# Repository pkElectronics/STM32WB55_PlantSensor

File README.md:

# STM32WB55_PlantSensor
Project goal (for the first stage) is to develop an IOT System based on the STM32WB SoC to monitor soil and air Moisture as well as environment temperature.
Therefore several components will be developed including a battery powered sensor to stick into your flower pots and a base station to display and log the measurements from the sensors. 
Communication between the sensors and the base will be done via bluetooth mesh. Later more kinds of sensors may be developed as well.

All Hardware Design Files licensed under CC BY-NC 4.0 

https://creativecommons.org/licenses/by-nc/4.0/legalcode

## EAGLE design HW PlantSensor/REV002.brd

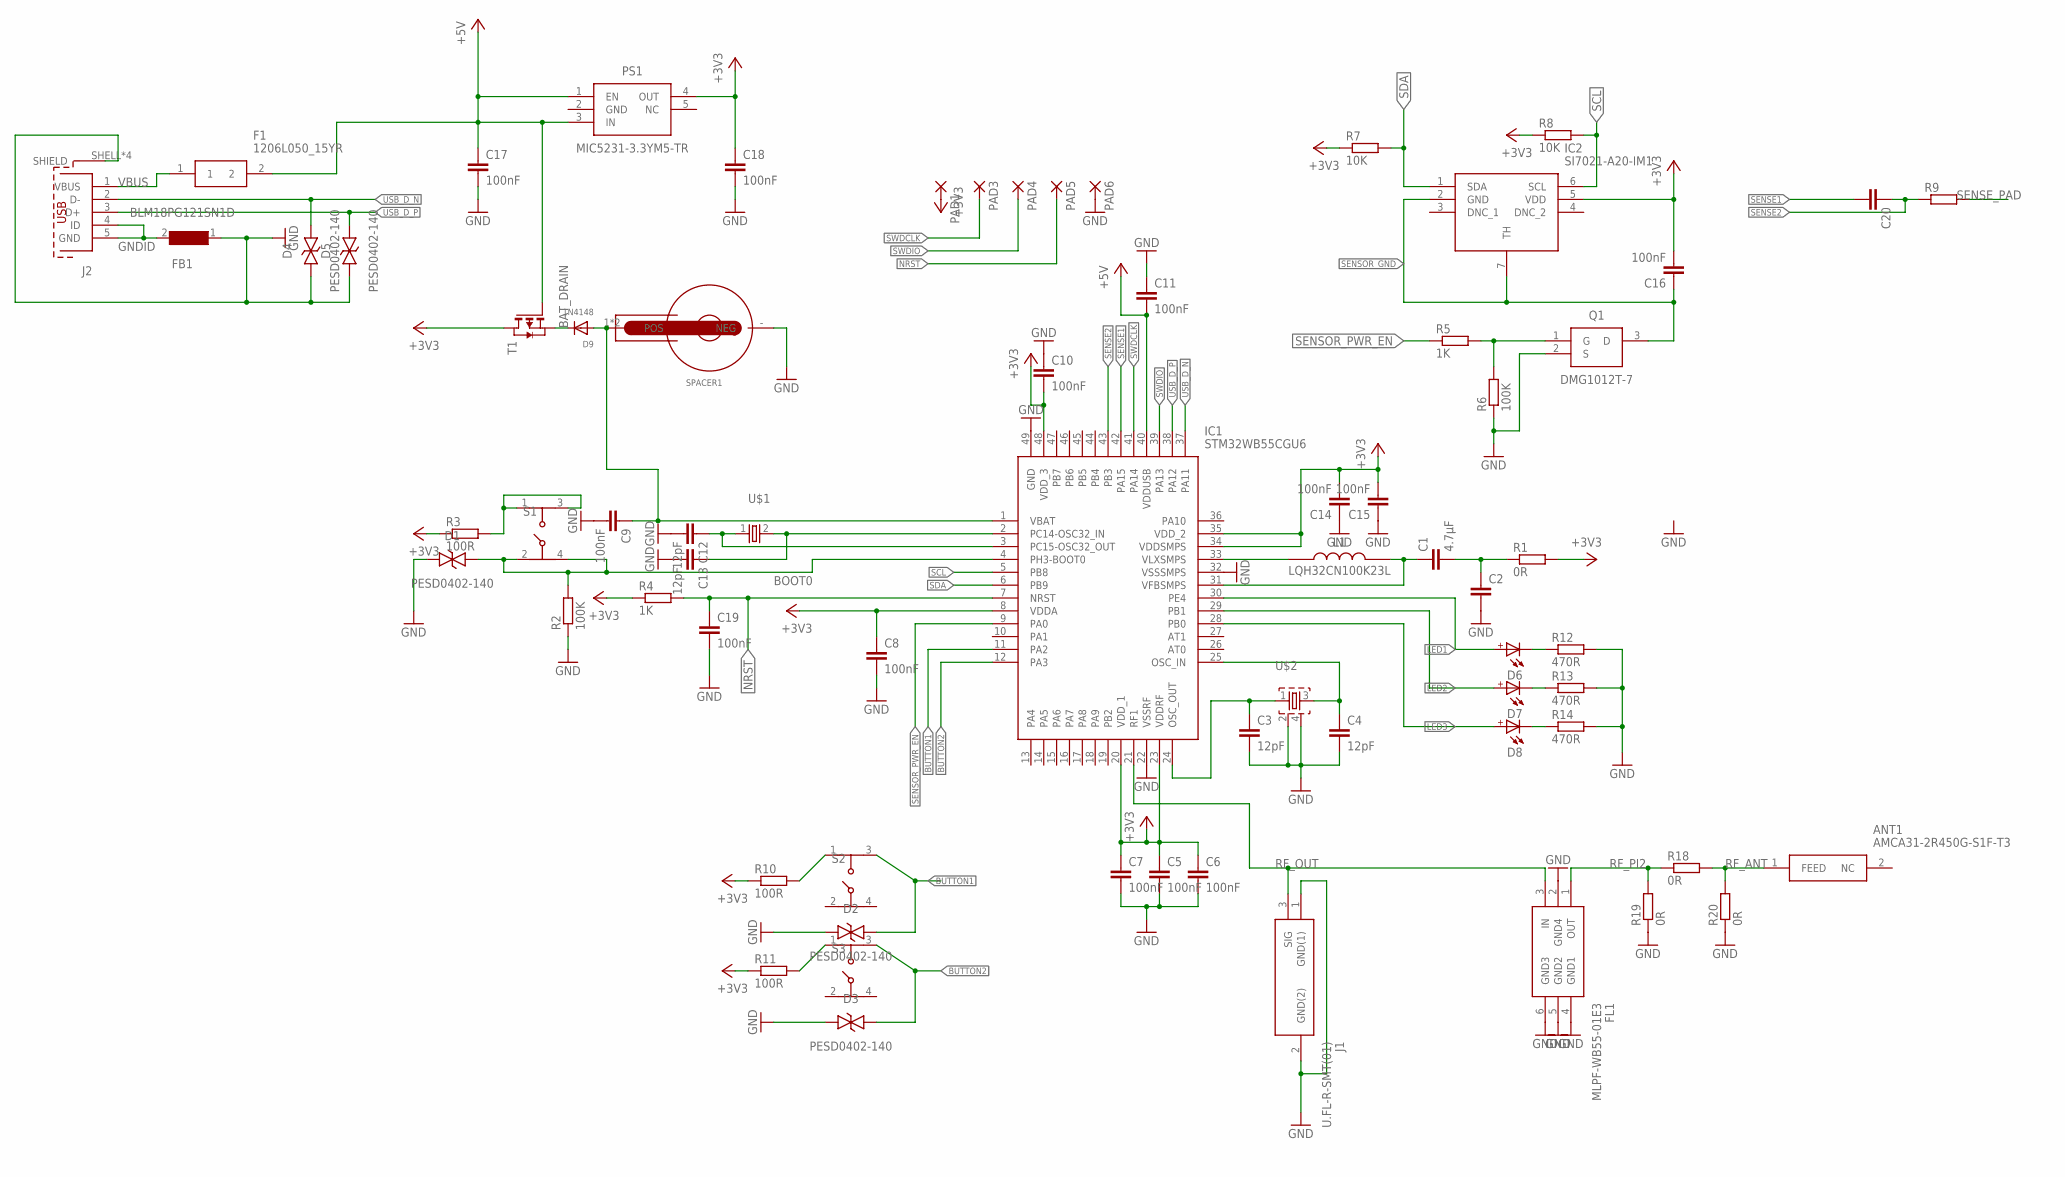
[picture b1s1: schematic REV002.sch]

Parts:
ANT1: AMCA31-2R450G-S1F-T3; ANTC3216X140N
C1: 4.7µF; C1210K
C2, C20: C-EUC0402K; C0402K
C3, C4, C12, C13: 12pF; C0402K
C5, C6, C7, C8, C9, C10, C11, C14, C15, C16, C17, C18, C19: 100nF; C0402K
D1, D2, D3, D4, D5: PESD0402-140; DIONC1005X43N
D6, D7, D8: WL-SMCD_0603_150060BS55040; WL-SMCD_0603
D9: 1N4148; SOD-323F
F1: 1206L050_15YR; FUSC3216X75N
FB1: BLM18PG121SN1D; BEADC1608X95N
FL1: MLPF-WB55-01E3; MLPFWB5501E3
IC1: STM32WB55CGU6; QFN50P700X700X65-49N
IC2: SI7021-A20-IM1; SON100P300X300X121-7N
J1: U.FL-R-SMT(01)
J2: 629105136821
L1: LQH32CN100K23L; INDPM3225X220N
PAD1, PAD3, PAD4, PAD5, PAD6: SMD2; SMD1,27-2,54
PS1: MIC5231-3.3YM5-TR; SOT95P270X145-5N
Q1: DMG1012T-7; SOT50P160X80-3N
R1, R18, R19, R20: 0R; R0402
R2, R6: 100K; R0402
R3, R10, R11: 100R; R0402
R4, R5: 1K; R0402
R7, R8: 10K; R0402
R9: R-EU_R0402; R0402
R12, R13, R14: 470R; R0402
S1, S2, S3: 434153017835
SPACER1: WA-BCMC_SMT_79523141; 79523141
T1: PMOSSOT23; SOT-23
U$1: XTAL_32KHZ; XTAL_3215_N
U$2: XTAL_32MHZ; BT-XTAL_2016_N

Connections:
+3V3: C5.1, C6.1, C7.1, C8.1, C10.2, C14.2, C15.2, C16.2, C18.1, IC1.8 (VDDA), IC1.20 (VDD_1), IC1.23 (VDDRF), IC1.34 (VDDSMPS), IC1.35 (VDD_2), IC1.48 (VDD_3), IC2.5 (VDD), PAD1.1, PS1.4 (OUT), R1.2, R3.1, R4.1, R7.1, R8.1, R10.1, R11.1, T1.1 (D)
+5V: C11.2, C17.1, F1.2, IC1.40 (VDDUSB), PS1.1 (EN), PS1.3 (IN), T1.3 (G)
BAT+: C9.1, D9.A, IC1.1 (VBAT), SPACER1.1 (POS), SPACER1.2 (POS)
BAT_DRAIN: D9.C, T1.2 (S)
BOOT0: D1.2 (A), IC1.4 (PH3-BOOT0), R2.2, S1.2 (3), S1.4
BOOT0_R: R3.2, S1.1, S1.3 (2)
BUTTON1: D2.2 (A), IC1.11 (PA2), S2.3 (2)
BUTTON1_R: R10.2, S2.1
BUTTON2: D3.2 (A), IC1.12 (PA3), S3.3 (2)
BUTTON2_R: R11.2, S3.1
GND: C2.2, C3.2, C4.2, C5.2, C6.2, C7.2, C8.2, C9.2, C10.1, C11.1, C12.2, C13.2, C14.1, C15.1, C17.2, C18.2, C19.2, D1.1 (K), D2.1 (K), D3.1 (K), D4.1 (K), D5.1 (K), FB1.1, FL1.2 (GND4), FL1.4 (GND1), FL1.5 (GND2), FL1.6 (GND3), IC1.22 (VSSRF), IC1.32 (VSSSMPS), IC1.49 (GND), J1.1 (GND(1)), J1.2 (GND(2)), J2.SHELL (SHIELD), J2.SHELL1 (SHIELD), J2.SHELL2 (SHIELD), J2.SHELL3 (SHIELD), PAD6.1, Q1.2 (S), R2.1, R6.1, R12.2, R13.2, R14.2, R19.1, R20.1, SPACER1.- (NEG), U$2.2, U$2.4
GNDID: FB1.2, J2.4 (ID), J2.5 (GND)
LED1: D6.2 (A), IC1.30 (PE4)
LED1_R: D6.1 (C), R12.1
LED2: D7.2 (A), IC1.29 (PB1)
LED2_R: D7.1 (C), R13.1
LED3: D8.2 (A), IC1.28 (PB0)
LED3_R: D8.1 (C), R14.1
unnamed: C13.1, IC1.2 (PC14-OSC32_IN), U$1.2
unnamed: C12.1, IC1.3 (PC15-OSC32_OUT), U$1.1
NRST: C19.1, IC1.7 (NRST), PAD5.1, R4.2
OSC_IN: C4.1, IC1.25 (OSC_IN), U$2.3
OSC_OUT: C3.1, IC1.24 (OSC_OUT), U$2.1
RF_ANT: ANT1.1 (FEED), R18.2, R20.2
RF_OUT: FL1.3 (IN), IC1.21 (RF1), J1.3 (SIG)
RF_PI2: FL1.1 (OUT), R18.1, R19.2
SCL: IC1.5 (PB8), IC2.6 (SCL), R8.2
SDA: IC1.6 (PB9), IC2.1 (SDA), R7.2
SENSE1: C20.2, IC1.42 (PA15)
SENSE2: C20.1, IC1.43 (PB3), R9.1
SENSE_PAD: R9.2
SENSOR_GATE: Q1.1 (G), R5.2, R6.2
SENSOR_GND: C16.1, IC2.2 (GND), IC2.7 (TH), Q1.3 (D)
SENSOR_PWR_EN: IC1.9 (PA0), R5.1
SMPS: C1.2, C2.1, R1.1
SWDCLK: IC1.41 (PA14), PAD3.1
SWDIO: IC1.39 (PA13), PAD4.1
USB_D_N: D4.2 (A), IC1.37 (PA11), J2.2 (D-)
USB_D_P: D5.2 (A), IC1.38 (PA12), J2.3 (D+)
VBUS: F1.1, J2.1 (VBUS)
VFBSMPS: C1.1, IC1.31 (VFBSMPS), L1.2
VLXSMPS: IC1.33 (VLXSMPS), L1.1

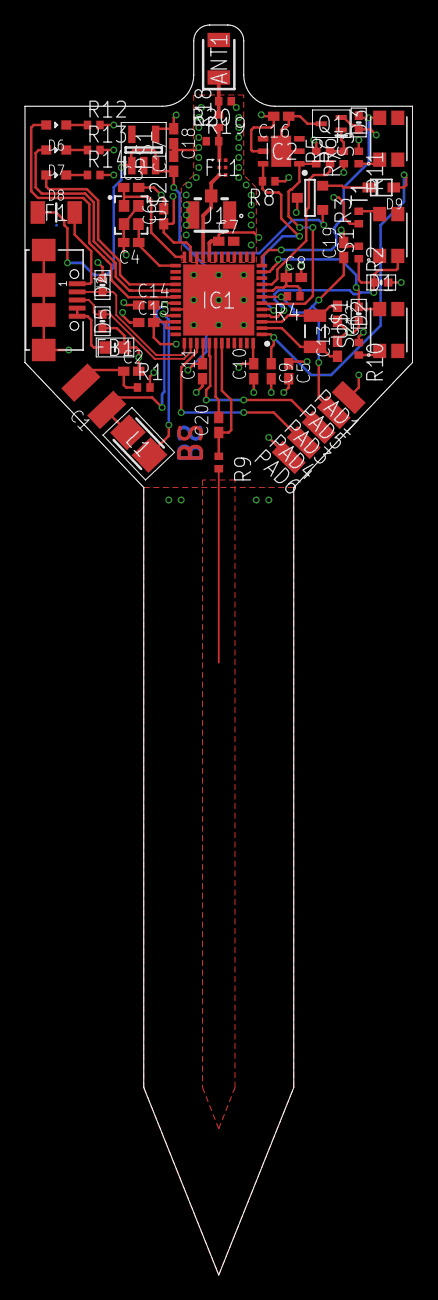
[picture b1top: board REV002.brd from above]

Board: 4 copper layers, 31.0 x 100.0 mm, 69 parts (1 on the bottom side), 41 nets.

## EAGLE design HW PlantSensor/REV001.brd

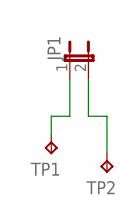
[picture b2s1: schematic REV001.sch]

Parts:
JP1: JP1E; JP1
TP1, TP2: TPTP06SQ; TP06SQ

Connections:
1: JP1.1, TP1.TP
2: JP1.2, TP2.TP

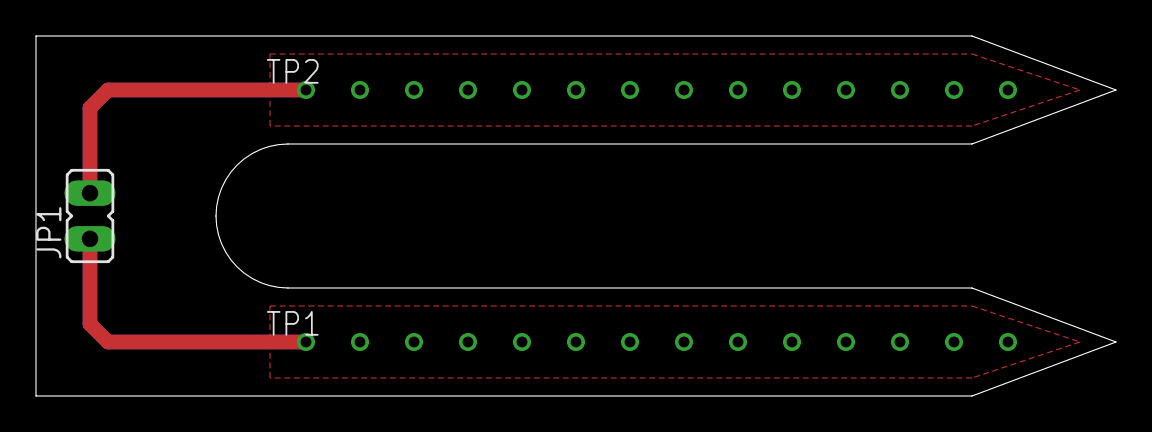
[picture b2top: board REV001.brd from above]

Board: 2 copper layers, 60.0 x 20.0 mm, 3 parts (0 on the bottom side), 2 nets.

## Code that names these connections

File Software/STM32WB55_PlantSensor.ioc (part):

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Mcu.Name=STM32WB55CGUx
Mcu.Package=UFQFPN48
Mcu.UserName=STM32WB55CGUx
PA0.GPIOParameters=GPIO_Label
PA0.GPIO_Label=SENSOR_PWR
PA0.Signal=GPIO_Output
PA11.Mode=Device
PA11.Signal=USB_DM
PA12.Mode=Device
PA12.Signal=USB_DP
PA13.Mode=Serial_Wire
PA13.Signal=SYS_JTMS-SWDIO
PA14.Mode=Serial_Wire
PA14.Signal=SYS_JTCK-SWCLK
PA15.GPIOParameters=GPIO_Label
PA15.GPIO_Label=SENSE1
PA15.Signal=GPIO_Input
PA2.GPIOParameters=GPIO_Label
PA2.GPIO_Label=BUTTON1
PA2.Signal=GPIO_Output
PA3.GPIOParameters=GPIO_Label
PA3.GPIO_Label=BUTTON2
PA3.Signal=GPIO_Output
PB0.GPIOParameters=GPIO_Label
PB0.GPIO_Label=LED3
PB0.Signal=GPIO_Output
PB1.GPIOParameters=GPIO_Label
PB1.GPIO_Label=LED2
PB1.Signal=GPIO_Output
PB3.GPIOParameters=GPIO_Label
PB3.GPIO_Label=SENSE2
PB3.Signal=GPIO_Input
PB8.Mode=I2C
PB8.Signal=I2C1_SCL
PB9.Mode=I2C
PB9.Signal=I2C1_SDA
PC14-OSC32_IN.Mode=LSE-External-Oscillator
PC14-OSC32_IN.Signal=RCC_OSC32_IN
PC15-OSC32_OUT.Mode=LSE-External-Oscillator
PC15-OSC32_OUT.Signal=RCC_OSC32_OUT
PE4.GPIOParameters=GPIO_Label
PE4.GPIO_Label=LED1
PE4.Signal=GPIO_Output
RCC.HSE_VALUE=32000000
RCC.SYSCLKFreq_VALUE=64000000
RCC.SYSCLKSource=RCC_SYSCLKSOURCE_PLLCLK
board=custom

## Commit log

2019-06-28 Initial Commit of Hardware Design
2019-11-08 Zwischencommit Software

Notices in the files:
parts and their libraries:
Wurth_Elektronik_Electromechanic_Switch_: Copyright: Würth Elektronik
